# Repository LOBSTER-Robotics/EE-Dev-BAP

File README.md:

# EE-Dev-DAQ
Data Aqusition System for Underwater Communication

# Project Branching Strategy

This repository follows a structured branching model designed to keep hardware, software, and miscellaneous work isolated, organized, and scalable.

## Core Principle

The `main` (or `master`) branch is **protected and never modified directly**. It serves as the stable, top-level reference for the entire project.

All active development happens in subsystem-specific branches.

## Top-Level Branches

The repository is divided into four primary branches:

- `hardware/`
- `software/`
- `vhdl/`
- `misc/`

Each of these represents an independent subsystem of the project.

## Subsystem Branch Structure

Every subsystem branch follows the same internal structure:

- `<subsystem>/main` — stable version of that subsystem (equivalent to a local "master")
- `<subsystem>/development` — integration branch for ongoing development
- `<subsystem>/feature/*` — feature‑specific branches

### Example (VHDL)

- `vhdl/main`
- `vhdl/development`
- `vhdl/feature/uart-module`
- `vhdl/feature/sdram-controller`

## Development Workflow

1. New work starts in a feature branch:
   - Branch from `<subsystem>/development`

2. Feature development:
   - Work is done in `<subsystem>/feature/*`

3. Integration:
   - Feature branches are merged into `<subsystem>/development`

4. Stabilization:
   - Once stable, `development` is merged into `<subsystem>/main`

5. System‑wide integration (optional/manual):
   - Changes from subsystem `main` branches may be selectively reflected in the global `main` branch if needed

## Important Rules

- Do not commit directly to `main`
- Do not mix hardware, software, vhdl, and misc changes in the same branch
- Keep feature branches focused and short‑lived
- Use pull requests for all merges
- Each subsystem evolves independently through its own branching lifecycle

## Why This Model?

This structure allows:

- Parallel development across domains
- Clear separation of concerns
- Reduced merge conflicts
- Independent release cycles per subsystem

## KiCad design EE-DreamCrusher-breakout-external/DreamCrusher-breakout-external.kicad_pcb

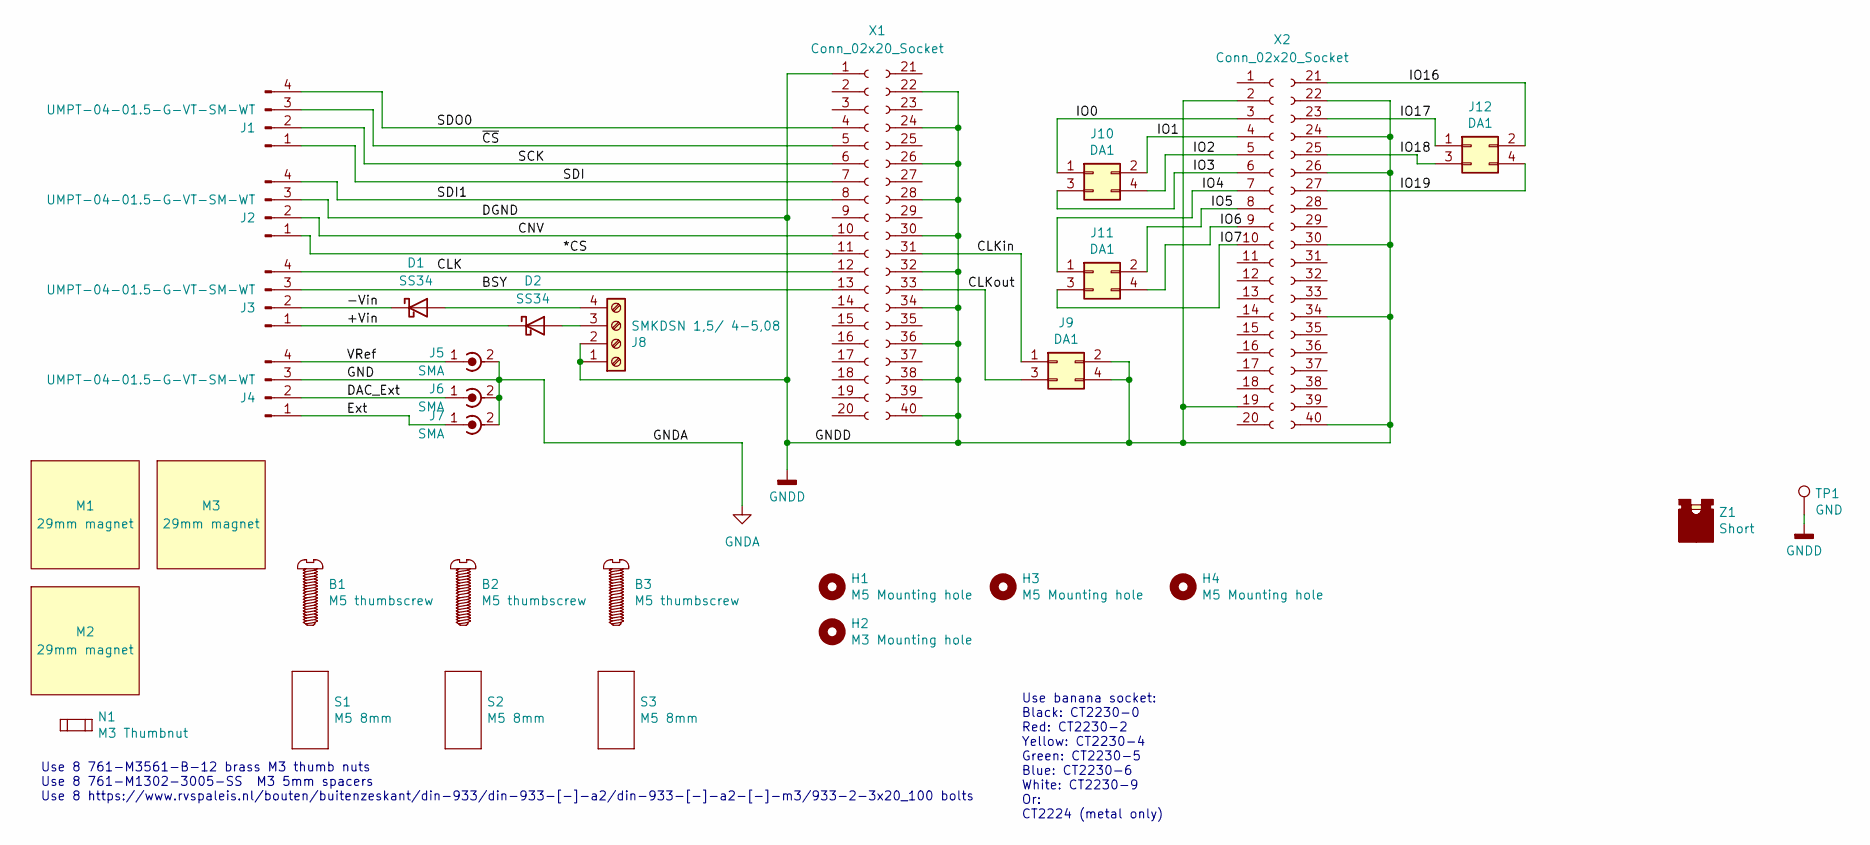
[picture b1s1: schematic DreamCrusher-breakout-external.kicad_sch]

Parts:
B1, B2, B3: M5 thumbscrew; ThumbScrew-M5; Part number M3451-SS
D1, D2: SS34; D_SMA; Part number SS34
H1, H3, H4: M5 Mounting hole; MountingHole_5.3mm_M5_NoMask
H2: M3 Mounting hole; MountingHole_3.2mm_M3_NoMask
J1, J2, J3, J4: UMPT-04-01.5-G-VT-SM-WT; Part number UMPT-04-01.5-G-VT-SM-WT-K
J5, J6, J7: SMA; SMA_Wurth_60312002114503_Vertical; Part number 60312002114503
J8: SMKDSN 1,5/ 4-5,08; TerminalBlock_Phoenix_SMKDSN-1,5-4-5.08_1x04_P5.08mm_Angled; Part number 1869237
J9, J10, J11, J12: DA1; PinHeader_2x02_P2.54mm_Vertical_Jumper; Part number 5-146281-2
M1, M2, M3: 29mm magnet; PotMagnet_RubberCoating_M5_D29_O7; Part number Potmagneet met rubber coating met inwen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
N1: M3 Thumbnut; ThumbNut-M3; Part number M3561-B-12
S1, S2, S3: M5 8mm; Spacer_M5_8mm; Part number M0657-5-AL
TP1: GND; TestPoint_Pad_D1.0mm
X1, X2: Conn_02x20_Socket; PinSocket_2x20_P2.54mm_Vertical_SMD; Part number M20-7812045
Z1: Short; SNT-100-BK-H; Part number SNT-100-BK-H

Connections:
/*CS: J2.1, X1.11
/+Vin: D2.1 (K), J3.1
/-Vin: D1.1 (K), J3.2
/BSY: J3.3, X1.13
/CLK: J3.4, X1.12
/CLKin: J9.1, X1.31
/CLKout: J9.3, X1.33
/CNV: J2.2, X1.10
/DAC_Ext: J4.2, J6.1 (In)
/Ext: J4.1, J7.1 (In)
/IO0: J10.1, X2.3
/IO1: J10.2, X2.4
/IO2: J10.4, X2.5
/IO3: J10.3, X2.6
/IO4: J11.1, X2.7
/IO5: J11.2, X2.8
/IO6: J11.4, X2.9
/IO7: J11.3, X2.10
/IO16: J12.2, X2.21
/IO17: J12.1, X2.23
/IO18: J12.3, X2.25
/IO19: J12.4, X2.27
/SCK: J1.2, X1.6
/SDI: J1.1, X1.7
/SDI1: J2.4, X1.8
/SDO0: J1.4, X1.4
/VRef: J4.4, J5.1 (In)
/~CS: J1.3, X1.5
GNDA: J4.3, J5.2 (Ext), J6.2 (Ext), J7.2 (Ext)
GNDD: J2.3, J8.1, J8.2, J9.2, J9.4, TP1.1, X1.1, X1.22, X1.24, X1.26, X1.28, X1.30, X1.32, X1.34, X1.36, X1.38, X1.40, X2.2, X2.19, X2.22, X2.24, X2.26, X2.30, X2.34, X2.40
unnamed: D1.2 (A), J8.4
unnamed: D2.2 (A), J8.3

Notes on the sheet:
Use banana socket: Black: CT2230-0 Red: CT2230-2 Yellow: CT2230-4 Green: CT2230-5 Blue: CT2230-6 White: CT2230-9 Or: CT2224 (metal only)
Use 8 761-M3561-B-12 brass M3 thumb nuts Use 8 761-M1302-3005-SS M3 5mm spacers Use 8 https://www.rvspaleis.nl/bouten/buitenzeskant/din-933/din-933-[-]-a2/din-933-[-]-a2-[-]-m3/933-2-3x20_100 bolts

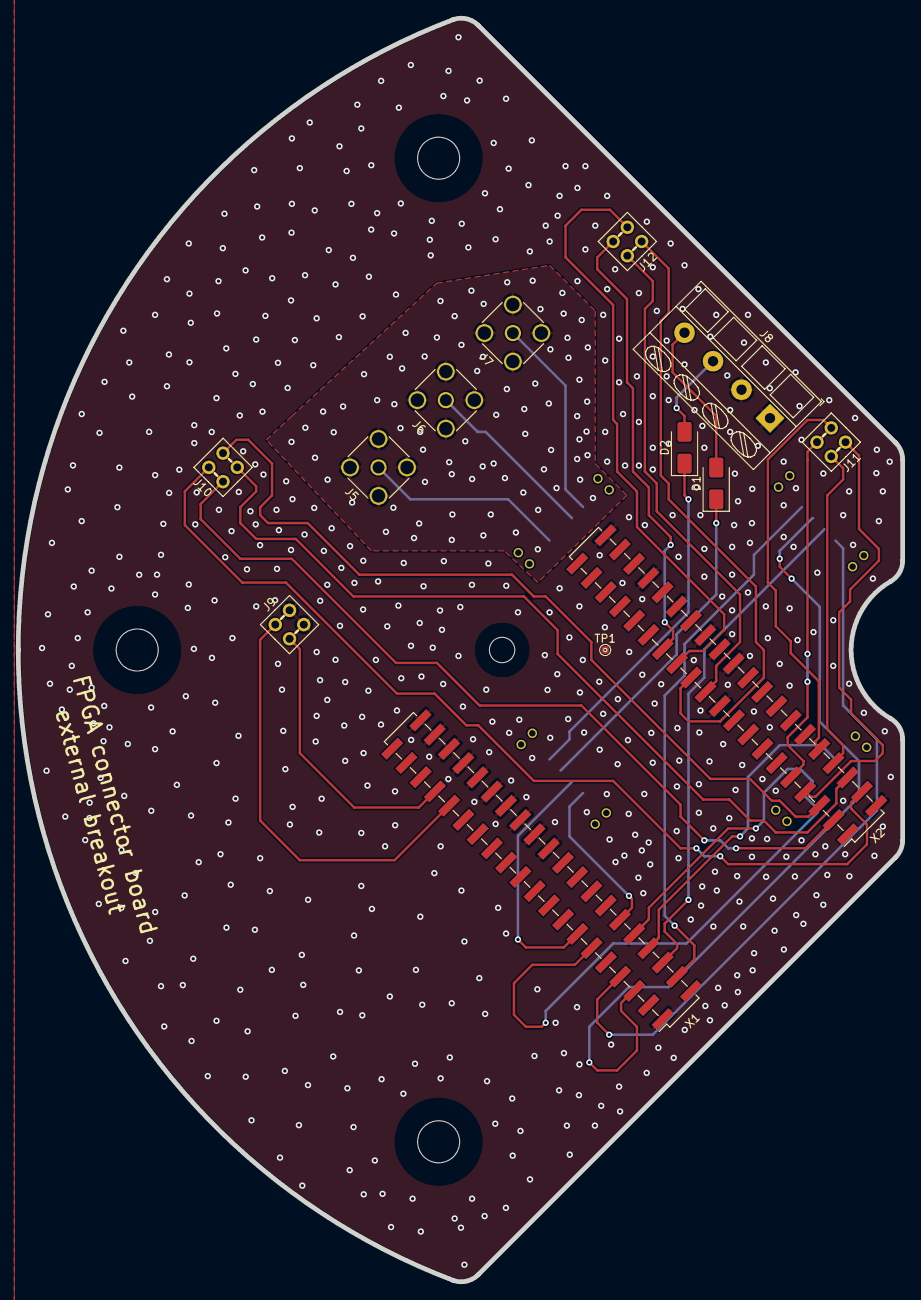
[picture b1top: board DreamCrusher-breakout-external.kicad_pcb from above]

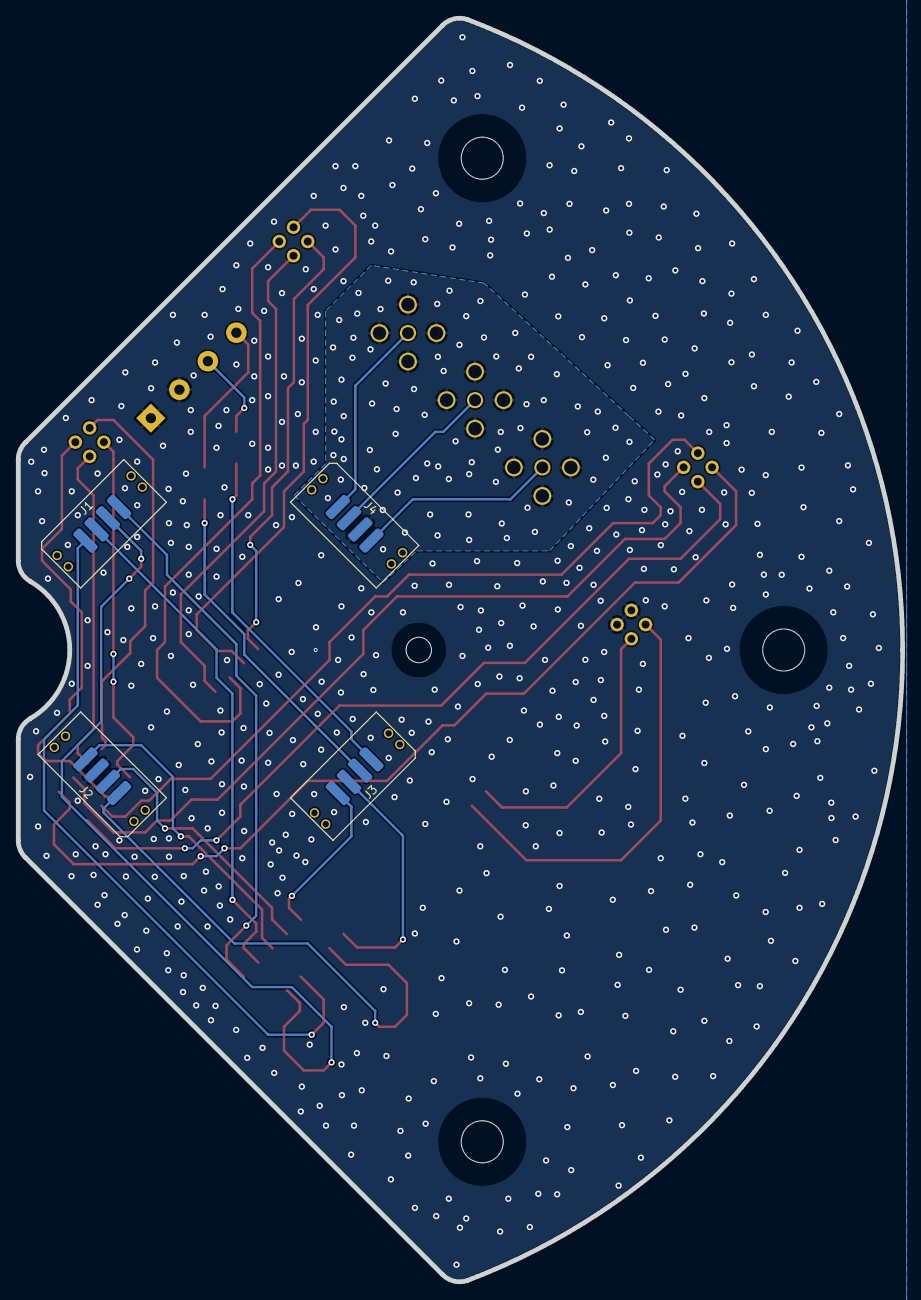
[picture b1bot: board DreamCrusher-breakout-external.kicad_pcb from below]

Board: 4 copper layers, 111.5 x 159.3 mm, 31 parts (10 on the bottom side), 32 nets.

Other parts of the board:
H7: M5 Mounting hole; MountingHole_5.3mm_M5_NoMask

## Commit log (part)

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2026-04-28 Added description of a model of working with the structure of the repo
2026-04-28 From Lobster Robotics projects
2026-04-28 From Lobster Projects
2026-04-28 Preparing the DAC symbol
2026-04-30 Added the ADC to the libs and implemented it
2026-05-01 Add SPI master entity declaration for DAC8811
2026-05-01 Implement Ethernet communication application with GUI
    This script is for testing the ethernet communication between the FPGA and your PC
2026-05-01 Removed temporary test file for testing push to git
2026-05-01 added DAC8811ICDGKT to library
2026-05-01 added opamp OPA277UA
2026-05-01 added OPA277 signle opamp
2026-05-01 Added the Refrence Voltage Source
2026-05-01 DAC schematic with opamp and top level added
2026-05-01 Remove src/spi_master_dac.vhd relocated to vhdl/
2026-05-01 Add FSMD architecture for spi-master-dac with registered look-ahead outputs
2026-05-04 Added the Vref supply, finished all of the top level connections
2026-05-04 Did the signal switching, finished ADC, misc changes to top
    Decided to go with solder jumpers instead of power switches bc power
    switches have no specs of linearity and they would add unnecessary
    complexity, development time, and routing problems.
    The calibration test has to be done only once and the chamber doesn't
    even have to be sealed for it, so it shouldn't add too much hassle.
2026-05-05 Added vhdl support in vscode using a devcontainer
    make sure you have docker desktop installed
2026-05-05 Refactor SPI master for N-channel independent SDI with shared CLK and CS
2026-05-05 Update for ethernet handling for the FPGA changed some indexing and representations
2026-05-05 Add testbench with three test cases for spi_master_dac
2026-05-05 Add devcontainer config to repo root for GHDL support
2026-05-05 DAC design done and added component potentiometer
2026-05-05 Finished switches, added calculations of the current consumption
2026-05-05 buffer added for vref to dac circuit
2026-05-05 Added PSUS, progress on the PSU circuit design, slight tweaks to the rest
2026-05-05 added decoupling capacitors to dac circuit
2026-05-06 cleaned up dac circuit a bit
2026-05-07 Added the ADC driver IC
2026-05-07 Progress on the implementation of the DAC driver
2026-05-07 removed unnecessary code and changed vhdl extension
2026-05-08 Fixed the switches, finished the adc amplifier, missing the filer to adc
2026-05-11 Added controller and controller test bench
2026-05-11 Added pdfs
2026-05-11 Finished the schematics. Fixed the comments that we recieved
2026-05-11 added voltage divider to dac circuits for opamps
2026-05-11 reverted last changes made to dac
2026-05-11 Ethernet tx part
    It has submodules of the tx part including testbenches. It aslo has a top entity of the tx part including a testbench.
2026-05-12 7v and -1.2V supplying opa277s
2026-05-12 Added negative voltage LDO and 7V LDO
2026-05-12 Finished
    Final touches, PSUs filtering, external connections, psu connections for
    the negative voltage, and the DAC higher voltage, and the negative
    voltage. Added an external connection directely to the DAC.
2026-05-12 added breakoutboard start
2026-05-12 Progress on the component placement
2026-05-13 Ethernet RX part
    modules and the top of rx, including testbenches
2026-05-13 schematic of breakout board almost finished but still need to add oscillator before pcb design can begin
2026-05-13 ADC working controller
2026-05-13 Added footprints from the Lobster librariries for the breakout connections
2026-05-13 Progress on fixing the remaining footprints and 3 models
2026-05-18 Progress on the layout
2026-05-19 DAC working controller
2026-05-19 Pregrezz
2026-05-20 Added signal reconditioning components and thier footprints
2026-05-20 added a top level behavioral architecture to the spi-master-adc
2026-05-21 Schematics for the clock reconditioning
2026-05-21 Finished the reconditioning circuit
2026-05-21 Added the components for the reconditioning to the pcb
2026-05-21 added RX integration and began fixing the timing issues
2026-05-21 Progress on the layout of the signal reconditioning circuit
2026-05-21 Layout mostly done
2026-05-21 Added the pin header
2026-05-21 Connected the pin header in the schematics
2026-05-21 Added the footprint
    My libraries are fucked for some reason so I have to change machines to
    pull footprints and add components
2026-05-21 Almost finished the layout. Did all of the power and top layer
2026-05-22 added behavioural architeture for the config block of the adc spi master
2026-05-22 Progrezz
2026-05-22 Stiching ground
2026-05-25 Finished the layout
    Modified ground planes separation, finished stiching, fixed drc errors
2026-05-26 Added final fifo entities
2026-05-26 Added zips
2026-05-26 Added biasing and termination resistors for the logic gates
2026-05-26 added odb file
2026-05-26 ADDED: SPI controller with proper fsm design and testbench ( for 50MHz input clock)
2026-05-26 DIR changes
2026-05-26 Added components part numbers and stuff. Added termination resistors
2026-05-26 Added python files to it
2026-05-26 added part numbers
2026-05-26 Removed garbage
2026-05-26 Changed the supplier of the ADC to mouser
2026-05-27 RX ath timing isues fixed
2026-05-27 git was doing weird so...
2026-05-27 correction tx path instead of rx path
2026-05-27 Different changes
2026-05-27 Added behavioral architecture for the Acquisition phase and a testbench for the whole system
2026-05-27 test board programming lattice file
2026-05-28 Begun testing the RX on the FPGA
2026-05-28 added tx sim forfpga
2026-05-29 ADDED: behavioral file for the full path test (FIFO-DAC)
2026-05-29 ADDED: bahvioural top level + lpf file for DAC baseline validation (FIFO-DAC)
2026-05-29 Fixed the RX part it now works still need to do ip address filtering
2026-05-29 UART with echo test
2026-05-29 Added FIFOsm_DAC.vhd
2026-05-29 Fixed merges
2026-05-29 Modified the top level for the correct fifo entity
2026-05-29 added uart test to send
2026-05-29 Project update
2026-06-01 Added filter to UDP_RX
    now filters mac and ip adress. Port stays the same
2026-06-01 Update UDP_RX_AXItoFIFO_filtered_constants.vhd
    changed constants to generics
2026-06-01 Update UDP_FIFO_AXI.vhd
    added max payload size
2026-06-01 strips the crc bytes from the received input
2026-06-01 Removed most timing issues now comes correctly from the testbench
2026-06-01 dac test based on Cyclone 10 LP
2026-06-02 gitignore for quartus files
2026-06-02 Create simple_eth_frame_gen.vhd
    for testing transmit with static ethernet header
2026-06-02 sclk gated with '1' and top level added for a slower spi clock
2026-06-03 Update UDP_FIFO_AXI.vhd
    read comment for final fix. Also fixed pld_cnt to only count when data is actually send
2026-06-03 Added ADC and DAC to top level
2026-06-03 Data validation done
2026-06-03 dac test with a slow clock and the 50MHZ sclk, harcoded values from 0x0000 to 0xFFFF, succesful output on the dac
2026-06-03 Added python code to send data to the FPGA
2026-06-04 Added debug led signal for FPGA debugging
2026-06-04 Create UDP_RX_AXItoFIFO_static_filters_separate_cnt.vhd
    this one maby works with no timming isues?
2026-06-04 added receive to gui
2026-06-05 Update so recieve works reliably
2026-06-05 git ignore update
2026-06-05 ADC test
2026-06-05 ADC timing issues fix
2026-06-05 ADC Process input fix
2026-06-08 last version of the top level for the dac test
2026-06-08 Started DAC implementation
2026-06-08 Moved files for cleanup
2026-06-09 Added bodges
2026-06-09 Remove duplicate case-conflicting DAC SPI file
2026-06-09 This sends data at a rate that should not completly fill the fifo
2026-06-10 DAC tested with a fifo and a counter
2026-06-10 c++ implementation for pc comms
2026-06-10 Create PinoutForBreakoutboardFPGA.txt
    new pin out for breakout and FPGA
2026-06-10 added blockdiagrams
2026-06-11 got ethernet and adc working still need implementation
2026-06-11 implementation full version 1
2026-06-11 Dac pcb tested with a ramp and a sine wave
2026-06-11 new spi-master-dac that works based on the external clock on the board
2026-06-11 added more leniant timing to the singals in the conversion state
2026-06-11 Reduced the output voltage of the CNV reconditioned signal for the ADC
2026-06-11 changess
2026-06-11 Large fifo full out of ADC controller and added drawio files
2026-06-11 Edit enable from fifo
2026-06-11 Added lattice fifo and removed ext clock out
2026-06-11 PIN_FOR _BREAKOUT BOARD BODGED
2026-06-12 High impedance added for dac
2026-06-12 modified top_rx to test the dac with reclocking
2026-06-12 pc ethernet update
2026-06-12 adc tested on board
2026-06-12 cs assert early to compensate for reclocking delay
2026-06-14 added CS compensation for reclocking delay
2026-06-14 .txt files for testing
2026-06-14 ADDED : harcoded tests (ac sweep, dc ramp, 1kHz sine wave at full amplitude
2026-06-14 Testing live update
2026-06-14 ethernet
2026-06-15 sine 1khz test
2026-06-16 Final tests
2026-06-16 Blockdiagrams
